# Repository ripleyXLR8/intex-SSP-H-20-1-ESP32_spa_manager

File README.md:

# WORK IN PROGRESS

# Intex SSP-H-20-1 ESP32 Spa Manager

**WARNING 1 : The circuit in this project uses main voltage (220-240 Volt AC in western Europe). This can be deadly if not handled properly! You can easily hurt yourself as well. Build this circuit at your own risk.**

**WARNING 2 : Never ever ever power this circuit directly without a GFCI outlet (differential circuit breaker). Remember this wircuit will be used in a wet environnement. If you don't understand this, please watch this video https://www.youtube.com/watch?v=SHGo-52wCDc&t=63s and get some electrical knowledge about ground protection.**

**WARNING 3 : This project is still a work in progress, this page is a kind of building log, I haven't finish the board building and installation for the moment. Watch the issues page to see what is working and what is not.**

This project aims to build a replacement for the motherboard of the Intex SSP-20 Spa (it may work with other Intex spa and could be used to build a spa from scratch, but this is not the purpose of this page). My goal was to be able to control the spa remotely and integrate it in my domotic system. The board communicates over the MQTT protocol and publishes Home Assistant MQTT auto-discovery messages, so it integrates out of the box with Home Assistant (and works with any MQTT-based system such as Jeedom https://www.jeedom.com/). The second goal of this project is to improve the reliability of this spa and specificaly to solve a random E95 or E9X error problem. My spa was still under waranty when i started this project so I tried to be as stealth as possible.

## 1) Intex motherboard reverse engineering
Below the annotate picture of the motherboard with my understanding of its working principle. Since the card is labeled, everything is pretty straight forward except the descaler system and the pump system (the upper terminal barrier connector on the board).

### a) Sensors
There are 5 sensors connected to the board, 2 temperature sensors (black and white connectors), 2 flow sensors (red and green connectors) and 1 temperature fuse (yellow connector). They are all connected with a 3 pins JST like connector (it looks like a JST XH 3P but the JST XH 3P doesn't have a lock mecanism).

#### Temperature sensors
Both temperature sensors are negative temperature coefficient (NTC) thermistore, it means that the resistance of the thermistore decreases with an increase in temperature.

- The temperature sensor 1 is installed at the intake of the water pump so it reads the water temperature and it is use to regulate the water temperature from 20°C to 40°C.

- The temperature sensor 2 is installed in the core of  heating elements and its function is to detect overheating over 50°C and shut down the heating if necessary.

Since I'm reading a resistance value and not a temperature, I need to do some calibration (i.e. find a relation between the resistance I'm measuring and the temperature). To measure the real temperature of the water in the spa I connected a DS18B20 thermal sensor in place of the LCD panel. Then I have recorded the temperature of the water and the resistance of both integrated temperature probe of the spa during the heating process of the spa from 18°C to 40°C. The resut once smoothed is the curve presented below. (smoothing is mandatory since the ADC of the ESP32 is pretty noisy...)

I first tried to use the Steinhart-Hart equation https://fr.wikipedia.org/wiki/Relation_de_Steinhart-Hart but O did not get good results using this equation, especialy from 34 to 38 degrees.

Since I'm observing that the curve is pretty linear from 18 to 38 degrees, and that the value of the resistance is 0 for 40°C, I tried a linear regression. The result is pretty decent with a R=0,9926.

The equation is T = -276,38*R + 10513

You can also try a logarithmic regression an get the following equation : T = -7750*Ln(R) + 28589 

#### Temperature fuse
One temperature fuse is installed just below heating elements. I cannot test the triggering temperature but it seems that in normal condition the fuse let the current pass and if the temperature goes over 84°C then the fuse burn and the current stop passing and shut down the heating.

#### Flow sensors
Both flow sensors let the current pass only if flow is detected, they ensure that no heating is activated if there is no flow detected in the system.

### b) Power supply, relays and other parts
All the power cable (input and outputs) are connected by a barrier terminal block. We will use the same connector on our board because we don't want to alter the power cable and change their connector.

#### Heating elements
There is two heating element in the spa for a total power of 2000 Watts. They are directly powered by a relay allowing 220VAC to pass trough the heating element.
Please note that in normal condition :
- The water pump is always powered when heating. Any flow interruption signaled by the flow sensor result in an error and the heating stops.
- When you push the heating button the heating doesn't start immediately, the water pump starts and then a couple seconds after the heater 1 is powered then a couple seconds later the heater 2 starts.
- The heater 2 is shut-down if the jet pump is activated.

#### Jet pump
The jet pump is directly powered by a relay allowing 220VAC to pass trough the pump and pumping air into the Spa.

#### Water pump
The water pump is powered by 12VAC but before that a relay allows 220VAC to flow through a dual output 12VAC transformer (see the drawing above). The first output is send to a closed relay and the second output of the transformer goes into a full bridge rectifier producing 12VDC send to activate the relay and let the 12VAC flow into the water pump. It seems that the only goal of this system is to allow the descaling system to start at the same time as the pump (see below the descaling system). On this version on the board we will not implement the descaling system (maybe on the next version) so we will power the pump directly from the output transformer. (connection of A and B wires to C and D wires)

#### Control panel
I will replace the control panel with an external control box connected through the enclosure of the spa with an IP68 SP21-12 connector. (available here : https://www.amazon.com/gp/product/B071R6RSN6/ref=ppx_yo_dt_b_asin_title_o00_s00?ie=UTF8&psc=1)

#### Descaler system
It seems that this spa is equiped by a magnetic descaling system. Here is the wikipedia page on this technology (https://en.wikipedia.org/wiki/Magnetic_water_treatment). I cannot find the type of signal send to this device, it seems that the signal is AC with a modulation of amplitude. I will maybe investigate it later... so this function has not been implemented on the replacement board.

## 2) Designing the replacement board
### a) Working principle
An ESP32 (DevKitc) is the heart of the system. It allows us to connect : 
- 2 temperature sensors on 2 analog inputs,
- 2 flow sensors on 2 digital inputs,
- 1 temperature fuse on 1 digital input,
- 5 buttons on 5 digital input (PUMP, HEATING, JET, +, -),
- 1 LCD display on 2 digital inputs (I2C protocol),
- 4 power relays on 4 digital inputs.

Relays, LCD, temperature sensors, flow sensors, and buttons will not be powered from the 5 Volt pin of the arduino, we will use directly the 5 Volt DC power supply to power them directly.

The integrated wifi chip also allow us to connect to the wifi and the MQTT server to send and receive data.

### b) Electrical drawing
I used Eagle 8.2.2 to design the replacement board, below is the electrical drawing. The eagle files will be available soon.

### c) Board schematic
I wanted the board to be easily produce at home by anybody so I choose to use a single side PCB with plated-trhough holes (PTH) components. SMD component will be a also good choice, but I know that occasionnal welder are more at ease with PTH components. The drilling size is 0.8mm, the width of the electrical tracks is 16mil (0.40mm) and the clearance is 10mil (0.25mm), theses parameters allows you to produce the board using the toner transfer method (this method requires very few tools).

Relays are integrated on the board to be integrated more easily in the original enclosure.

The original motherboard dimension are 10.5 cm x 17 cm, mounting hole are 5mm wide and are placed 4.5mm from the edge of the board. The PCB will be mounted using the same mounting screw used by the original motherboard (but I don't think I will be using the center plastic lock).

The power tracks (tracks going to relays) will carry a lot of current. The total power of the Spa announced by Intex is 2200 watts. I have made some measurement on the original board to see how much current is use by each component :

- Heater 1 : 6.70A (Peak at startup) / 3.70A (Cruise) @ 220 Volt AC
- Heater 2 : 7.00A (Peak at startup) / 4.00A (Cruise) @ 220 Volt AC
- Water pump : 0.16A @ 12 Volt AC (This measure include also de descaler) 
- Air pump : 5.50A (Peak at startup) / 3.60A (Cruise) @ 220 Volt AC

As we can see, if everything is running at the same time the spa can draw a total of 11.46A with a peak at startup of 19,36A which is a lot. In the original board there is some rules to avoid the spa to reach this high current drawing :

- Heater 1 and 2 have a 20 seconds startup delay between each other.
- Air pump and heater 2 can't run at the same time.

We will implement the same rules to our board so the maximum current draw will be around 8A with a peak around 11A when starting the heater or the pump. (Which is about what is announced by Intex around 2400 Watts). By dimension the track width for 10A, 2oz/ft copper, an ambiant temperature of 25°C and a maximum temperature elevation of 5 degrees, we find that we need a 2,36 mm (93mil) track width.

### d) Board production
Board schematic has been sent to PCBway a chinese PCB prototyping company. https://www.pcbway.com/. They can even populate your board with the component if you want them to do it.

The list of component with links to buy them is provided below :

## 5) How to configure and install the new control board
### a) Uploading the code and first-boot configuration
Open the lastest `*.ino` file within the Arduino IDE. You no longer need to edit WiFi or MQTT credentials in the code — they are configured at runtime through a captive WiFi portal (WiFiManager) and saved in the ESP32 flash memory.

The feature flags at the top of the sketch are enabled by default and normally don't need to be changed :
`const bool wifi_enable = true;`
`const bool mqtt_enable = true;`
`const bool ota_enable = true;`  // WiFi OTA: lets you upload future updates over the air, without opening the case

Place your ESP32 on a breadboard, select the ESP32 board, set the baudrate to 115200 and upload the code. Once the upload is finished, press the reset button of the board.

On first boot (or whenever it cannot reach a known WiFi network) the board starts a WiFi access point named **`Spa-Intex-Config`**. Connect to it with a phone or computer and a captive portal opens where you set :
- your WiFi network and password,
- the MQTT server address and port (default `1883`),
- the MQTT username and password (leave empty if your broker has no authentication),
- the **OTA password** that protects over-the-air firmware updates.

These settings are stored permanently in the ESP32 flash. To erase the saved WiFi configuration and force the portal to reopen, **hold the BOOT button (GPIO 0)** while resetting the board.

⚠️ **Set the OTA password.** If you leave it empty, anyone on your network can flash arbitrary firmware to a board that switches 2 kW of mains heaters. The board logs a red warning at start-up while the OTA password is unset.

If the board cannot connect to WiFi within the portal timeout (180 s) it falls back to an **offline mode** : the local heating, filtration and jet logic keeps running, but no remote control is available.

### b) Checking the board connection
Open the serial port monitor of the Arduino IDE and set the baudrate to 115200. You should see the start-up sequence and the IP of your board on the WiFi network. Once connected, you can also open a **Telnet** session to that IP (port 23) to watch the live dashboard remotely — it prints the temperature, target, thermostat/filtration/jet/heater states and the anti-short-cycle timer every few seconds.

If you have any error message during the start-up you should check your configuration in the WiFi portal.

### c) Controlling the spa over MQTT
The board uses MQTT only (the previous HTTP/REST interface has been removed). It publishes its full state as a JSON payload to the **`spa_intex/info`** topic, for example :

`{"flow_1":true,"flow_2":true,"temp_1":21.3,"temp_2":21.8,"target":35.0,"heartbeat":65065,"thermostat":false,"filtration":false,"heater":false,"jet":true,"fuse":true,"bypass_flow":false,"bypass_fuse":false}`

In that payload `fuse:true` means the thermal fuse reads intact (safe to heat) and `flow_1/flow_2:true` mean water flow is detected.

Command topics (publish `1` or `0`, or a number for the target) :
- `spa_intex/target` -> set the target temperature (°C, capped at 39 °C).
- `spa_intex/thermostat` -> enable/disable the temperature regulation (enabling it also turns filtration on). Accepts `1`/`0` or `heat`/`off`.
- `spa_intex/filtration` -> enable/disable the filtration (water pump).
- `spa_intex/jet` -> enable/disable the jet (air pump / bubbles).
- `spa_intex/reset` -> publish `1` to reboot the board after a 10 s delay.
- `spa_intex/bypass_flow` -> override the water-flow interlock (see safety section below).
- `spa_intex/bypass_fuse` -> override the thermal-fuse interlock (see safety section below).

On every successful MQTT connection the board also publishes **Home Assistant MQTT auto-discovery** messages (under the `homeassistant/...` topics), so the device appears automatically as "Spa Intex" in Home Assistant — no manual entity configuration required. The thermostat is exposed as a single **`climate`** entity (current temperature, target slider, off/heat mode and a heating/idle indicator); the filtration and jet are switches, and the two interlock overrides are switches in the *Configuration* section. (The thermostat + setpoint were previously two separate switch/number entities — these are now removed in favour of the climate card.)

### d) Safety interlocks and current limiting
The heating logic enforces several hardware-protection rules. The heater stays off unless **all** of these hold:
- the thermostat is enabled and the water is below target (with a ±1 °C hysteresis band),
- **water flow is detected** on both flow sensors (`flow_1` and `flow_2`),
- the **thermal fuse reads intact** (`fuse`),
- the water temperature is below the 39 °C safety ceiling,
- the 15-minute anti-short-cycle timer allows the change (bypassed once on the first cycle).

To limit the inrush current (the original board draws up to ~19 A peak with everything starting at once), the firmware reproduces the factory rules: **heater 2 starts only ~20 s after heater 1**, and **heater 2 never runs at the same time as the jet/air pump** (turning the jet on temporarily drops heater 2). The live dashboard (serial / Telnet) shows which interlock is currently blocking the heater.

**Input polarity must match your board.** The active levels are defined at the top of the sketch:
`#define FLOW_ACTIVE_LEVEL HIGH` (level read when water flows) and `#define FUSE_OK_LEVEL HIGH` (level read when the fuse is intact). They default to *high = active*; if your wiring is inverted, flip these two `#define`s, otherwise the interlocks will read backwards. A disconnected flow or fuse input is treated as "no flow / fuse tripped" and **blocks heating** (fail-safe) — so the thermal-fuse (yellow) and flow connectors must be wired and working for the spa to heat.

#### Bypassing a broken sensor
If a flow sensor or the thermal fuse is faulty and you knowingly want to keep heating until you can replace it, two MQTT overrides let you bypass the interlock without touching the code:
- `spa_intex/bypass_flow` -> publish `1` to ignore the water-flow check, `0` to restore it.
- `spa_intex/bypass_fuse` -> publish `1` to ignore the thermal-fuse check, `0` to restore it.

Both are exposed as switches in the **Configuration** section of the Home Assistant device ("Spa Bypass Debit" / "Spa Bypass Fusible"), reported in the `info` payload (`bypass_flow` / `bypass_fuse`), and shown on the serial/Telnet dashboard (`Securites : Fusible [ACTIVE/CONTOURNEE] | Debit [...]`) with a red warning when engaged.

⚠️ **A bypass resets to OFF on every reboot/power-cycle** — it is deliberately not persisted, so cycling power always restores full safety. Bypassing the thermal fuse removes overheat protection; the only remaining backstop is the 39 °C software ceiling on the regulation sensor. Use these overrides only as a temporary measure and never leave the spa unattended while a bypass is active.

### e) Removing the old control board
First, it is very important to DISCONNECT THE POWER CABLE of the Spa. Remove the four screws securing the spa cover and remove it. Then locate the cover of the control board, remove all the screws and remove the cover. On the control board remove all cable from the lower and upper terminal, from the sensors and from the control panel, then remove the four screws securing the board and remove it.

### f) Installation of the new control board
Remove the central plastic pin in order to install the new board into the enclosure and then install the new board using the 4 screws from the old board. Then connect the old cables on the new board. Here is a quick connection guide based on the color of my board (double check it with you board before powering up the spa) :

- Red connector -> Flow 1 connector
- Green connector -> Flow 2 connector
- White connector ->  Temperature 2 connector
- Black connector ->  Temperature 1 connector
- Yellow connector -> DO NOT CONNECT (it doesn't work currently)
- Connector 1 -> N terminal
- Connector 2 -> L terminal
- Connector 5 -> N of the pump terminal
- Connector 6 -> L of the pump terminal
- Connector 7 -> N of the jet terminal
- Connector 8 -> L of the jet terminal
- Connector 9 -> N of the heater 1 terminal
- Connector 10 -> L of the heater 1 terminal
- Connector 11 -> N of the heater 2 terminal
- Connector 12 -> L of the heater 2 terminal

Then you have to connect together some wires from the upper terminal and isolate all non connected wires before powering up the spa.
- Cable A must be connected with cable C
- Cable B must be connected with cable D

You should get something like that :

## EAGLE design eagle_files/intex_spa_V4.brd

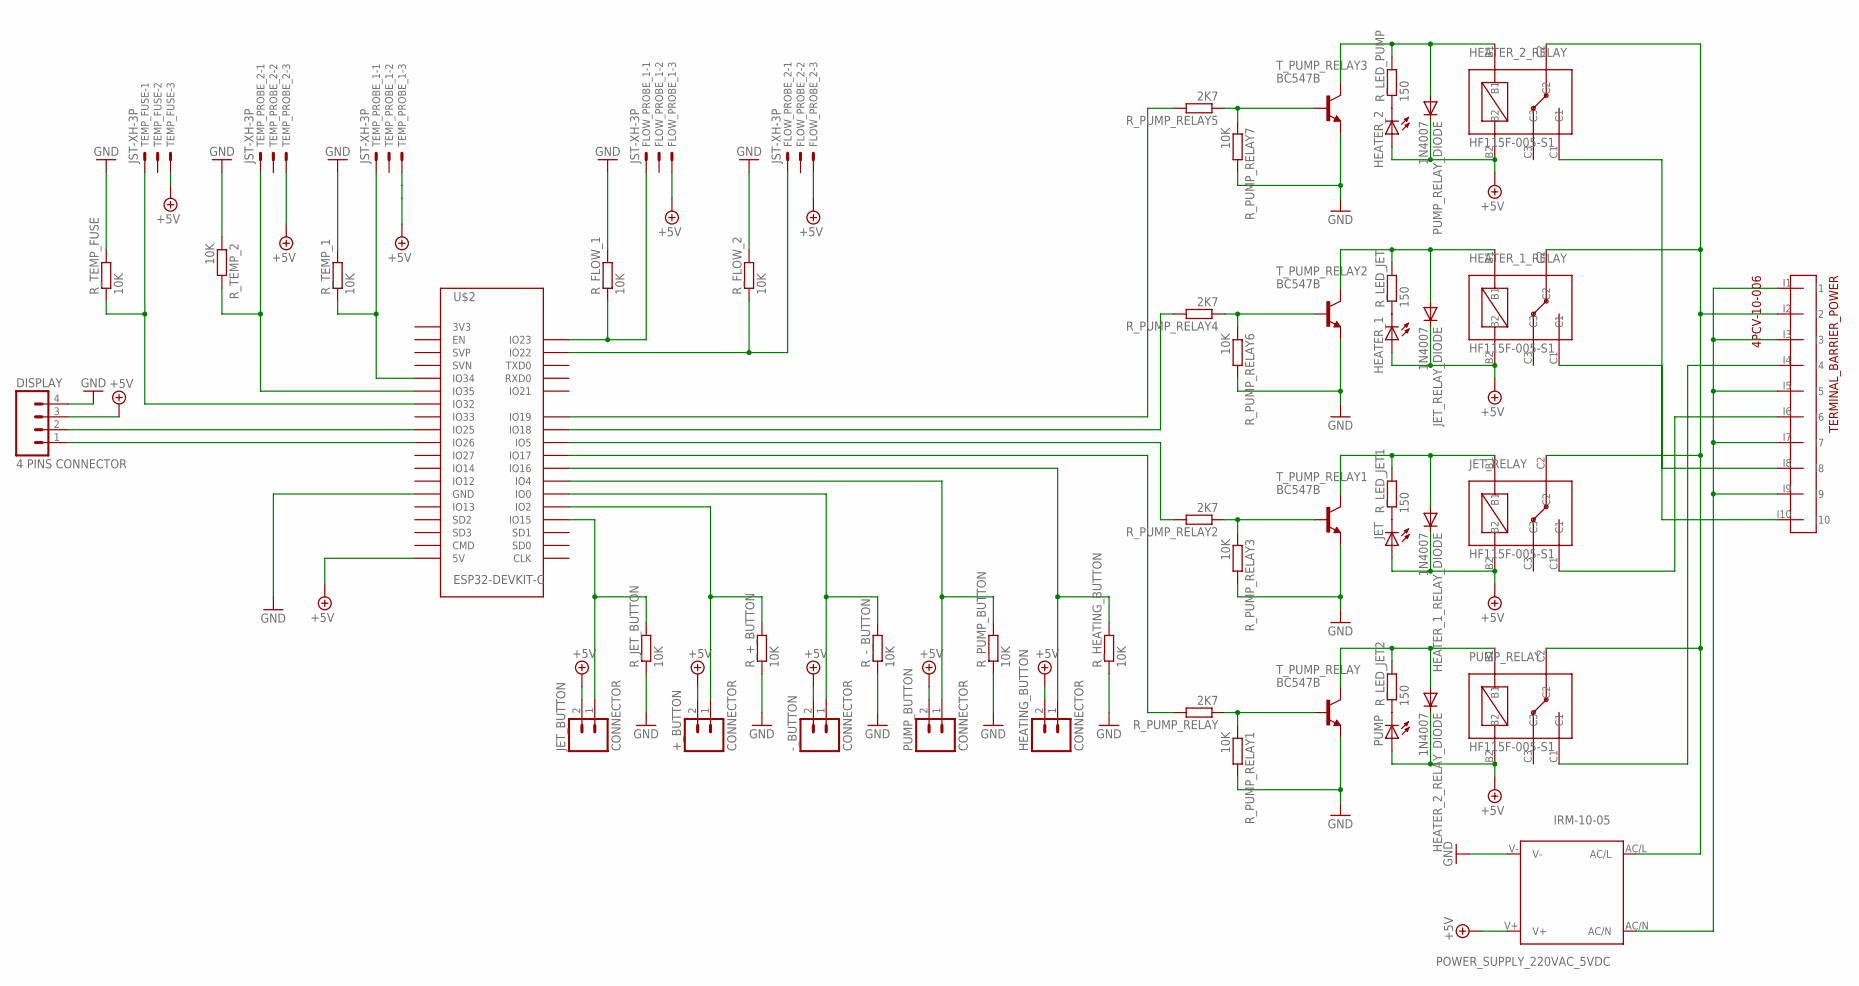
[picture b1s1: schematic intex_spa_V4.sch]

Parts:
+_BUTTON: CONNECTOR; JST-2-PTH-VERT
-_BUTTON: CONNECTOR; JST-2-PTH-VERT
DISPLAY: 4 PINS CONNECTOR; 1X04
FLOW_PROBE_1, FLOW_PROBE_2: JST-XH-3P; JST-XH-03-PACKAGE-LONG-PAD
HEATER_1, HEATER_2: LED3MM
HEATER_1_RELAY, HEATER_2_RELAY: HF115F-005-S1
HEATER_1_RELAY_DIODE, HEATER_2_RELAY_DIODE: 1N4007; DO41-10
HEATING_BUTTON: CONNECTOR; JST-2-PTH-VERT
JET: LED3MM
JET_BUTTON: CONNECTOR; JST-2-PTH-VERT
JET_RELAY: HF115F-005-S1
JET_RELAY_DIODE: 1N4007; DO41-10
POWER_SUPPLY_220VAC_5VDC: IRM-10-05; IRM_05/10
PUMP: LED3MM
PUMP_BUTTON: CONNECTOR; JST-2-PTH-VERT
PUMP_RELAY: HF115F-005-S1
PUMP_RELAY_DIODE: 1N4007; DO41-10
R_+_BUTTON: 10K; 0204/5
R_-_BUTTON: 10K; 0204/5
R_FLOW_1, R_FLOW_2: 10K; 0207/10
R_HEATING_BUTTON: 10K; 0204/5
R_JET_BUTTON: 10K; 0204/5
R_LED_JET, R_LED_JET1, R_LED_JET2: 150; 0204/5
R_LED_PUMP: 150; 0204/5
R_PUMP_BUTTON: 10K; 0204/5
R_PUMP_RELAY, R_PUMP_RELAY2, R_PUMP_RELAY4, R_PUMP_RELAY5: 2K7; 0204/5
R_PUMP_RELAY1, R_PUMP_RELAY3, R_PUMP_RELAY6, R_PUMP_RELAY7: 10K; 0204/5
R_TEMP_1, R_TEMP_2: 10K; 0207/10
R_TEMP_FUSE: 10K; 0207/10
TEMP_FUSE: JST-XH-3P; JST-XH-03-PACKAGE-LONG-PAD
TEMP_PROBE_1, TEMP_PROBE_2: JST-XH-3P; JST-XH-03-PACKAGE-LONG-PAD
TERMINAL_BARRIER_POWER: 4PCV-10-006
T_PUMP_RELAY, T_PUMP_RELAY1, T_PUMP_RELAY2, T_PUMP_RELAY3: BC547B; TO92
U$2: ESP32-DEVKIT-C

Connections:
+5V: +_BUTTON.2, -_BUTTON.2, DISPLAY.3, FLOW_PROBE_1.3, FLOW_PROBE_2.3, HEATER_1.A, HEATER_1_RELAY.B2, HEATER_1_RELAY_DIODE.C, HEATER_2.A, HEATER_2_RELAY.B2, HEATER_2_RELAY_DIODE.C, HEATING_BUTTON.2, JET.A, JET_BUTTON.2, JET_RELAY.B2, JET_RELAY_DIODE.C, POWER_SUPPLY_220VAC_5VDC.V+, PUMP.A, PUMP_BUTTON.2, PUMP_RELAY.B2, PUMP_RELAY_DIODE.C, TEMP_FUSE.3, TEMP_PROBE_1.3, TEMP_PROBE_2.3, U$2.5V
GND: DISPLAY.4, POWER_SUPPLY_220VAC_5VDC.V-, R_+_BUTTON.1, R_-_BUTTON.1, R_FLOW_1.2, R_FLOW_2.2, R_HEATING_BUTTON.1, R_JET_BUTTON.1, R_PUMP_BUTTON.1, R_PUMP_RELAY1.2, R_PUMP_RELAY3.2, R_PUMP_RELAY6.2, R_PUMP_RELAY7.2, R_TEMP_1.2, R_TEMP_2.1, R_TEMP_FUSE.2, T_PUMP_RELAY.1 (E), T_PUMP_RELAY1.1 (E), T_PUMP_RELAY2.1 (E), T_PUMP_RELAY3.1 (E), U$2.GND, U$2.GND2 (GND), U$2.GND3 (GND)
LEAD: HEATER_1_RELAY.C2, HEATER_2_RELAY.C2, JET_RELAY.C2, POWER_SUPPLY_220VAC_5VDC.AC/L, PUMP_RELAY.C2, TERMINAL_BARRIER_POWER.I2
LEAD_HEATER_1: HEATER_1_RELAY.C1, TERMINAL_BARRIER_POWER.I8
LEAD_HEATER_2: HEATER_2_RELAY.C1, TERMINAL_BARRIER_POWER.I10
LEAD_JET: JET_RELAY.C1, TERMINAL_BARRIER_POWER.I6
LEAD_PUMP: PUMP_RELAY.C1, TERMINAL_BARRIER_POWER.I4
unnamed: R_PUMP_RELAY.2, U$2.IO17
unnamed: R_TEMP_2.2, TEMP_PROBE_2.1, U$2.IO35
unnamed: FLOW_PROBE_2.1, R_FLOW_2.1, U$2.IO22
unnamed: R_PUMP_RELAY5.2, U$2.IO19
unnamed: R_PUMP_RELAY4.2, U$2.IO18
unnamed: R_PUMP_RELAY2.2, U$2.IO5
unnamed: HEATER_2.K (C), R_LED_PUMP.1
unnamed: R_TEMP_FUSE.1, TEMP_FUSE.1, U$2.IO32
unnamed: FLOW_PROBE_1.1, R_FLOW_1.1, U$2.IO23
unnamed: DISPLAY.1, U$2.IO26
unnamed: DISPLAY.2, U$2.IO25
unnamed: HEATING_BUTTON.1, R_HEATING_BUTTON.2, U$2.IO16
unnamed: -_BUTTON.1, R_-_BUTTON.2, U$2.IO0
unnamed: PUMP_BUTTON.1, R_PUMP_BUTTON.2, U$2.IO4
unnamed: +_BUTTON.1, R_+_BUTTON.2, U$2.IO2
unnamed: JET_BUTTON.1, R_JET_BUTTON.2, U$2.IO15
unnamed: JET.K (C), R_LED_JET1.1
unnamed: HEATER_1_RELAY_DIODE.A, JET_RELAY.B1, R_LED_JET1.2, T_PUMP_RELAY1.3 (C)
unnamed: HEATER_1.K (C), R_LED_JET.1
unnamed: PUMP.K (C), R_LED_JET2.1
unnamed: HEATER_2_RELAY_DIODE.A, PUMP_RELAY.B1, R_LED_JET2.2, T_PUMP_RELAY.3 (C)
unnamed: R_TEMP_1.1, TEMP_PROBE_1.1, U$2.IO34
unnamed: R_PUMP_RELAY.1, R_PUMP_RELAY1.1, T_PUMP_RELAY.2 (B)
unnamed: HEATER_1_RELAY.B1, JET_RELAY_DIODE.A, R_LED_JET.2, T_PUMP_RELAY2.3 (C)
unnamed: HEATER_2_RELAY.B1, PUMP_RELAY_DIODE.A, R_LED_PUMP.2, T_PUMP_RELAY3.3 (C)
unnamed: R_PUMP_RELAY2.1, R_PUMP_RELAY3.1, T_PUMP_RELAY1.2 (B)
unnamed: R_PUMP_RELAY4.1, R_PUMP_RELAY6.1, T_PUMP_RELAY2.2 (B)
unnamed: R_PUMP_RELAY5.1, R_PUMP_RELAY7.1, T_PUMP_RELAY3.2 (B)
NEUTRAL: POWER_SUPPLY_220VAC_5VDC.AC/N, TERMINAL_BARRIER_POWER.I1, TERMINAL_BARRIER_POWER.I3, TERMINAL_BARRIER_POWER.I5, TERMINAL_BARRIER_POWER.I7, TERMINAL_BARRIER_POWER.I9

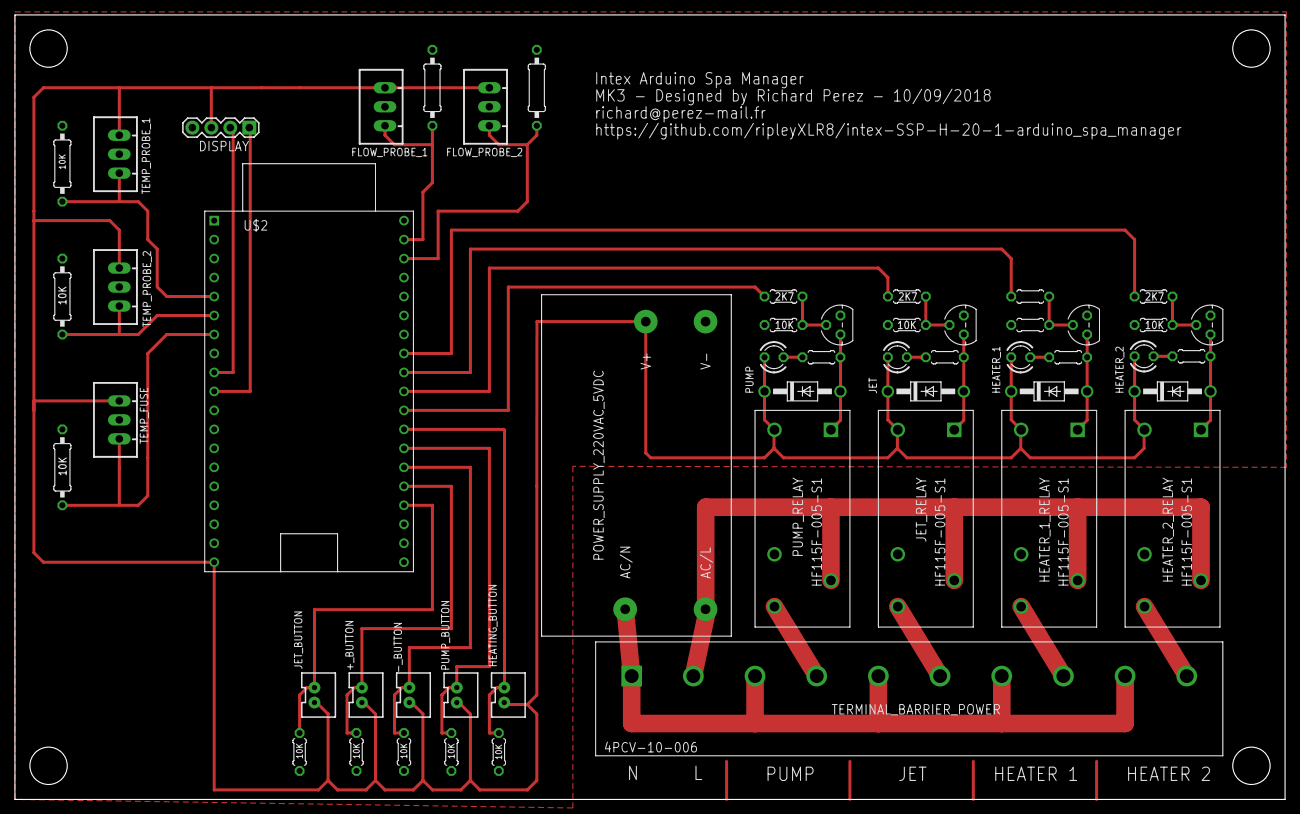
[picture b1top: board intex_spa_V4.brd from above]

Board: 2 copper layers, 170.0 x 105.0 mm, 52 parts (0 on the bottom side), 36 nets.

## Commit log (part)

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2019-05-02 Correction a small mistake in the drawing of the motherboard.
2019-05-02 Updating the electrical drawing with the last version of the board.
2019-05-02 Adding eagle files
2019-05-02 Not usefull anymore.

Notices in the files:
parts and their libraries:
SparkFun-Connectors: Licensing: Creative Commons ShareAlike 4.0 International - https://creativecommons.org/licenses/by-sa/4.0
